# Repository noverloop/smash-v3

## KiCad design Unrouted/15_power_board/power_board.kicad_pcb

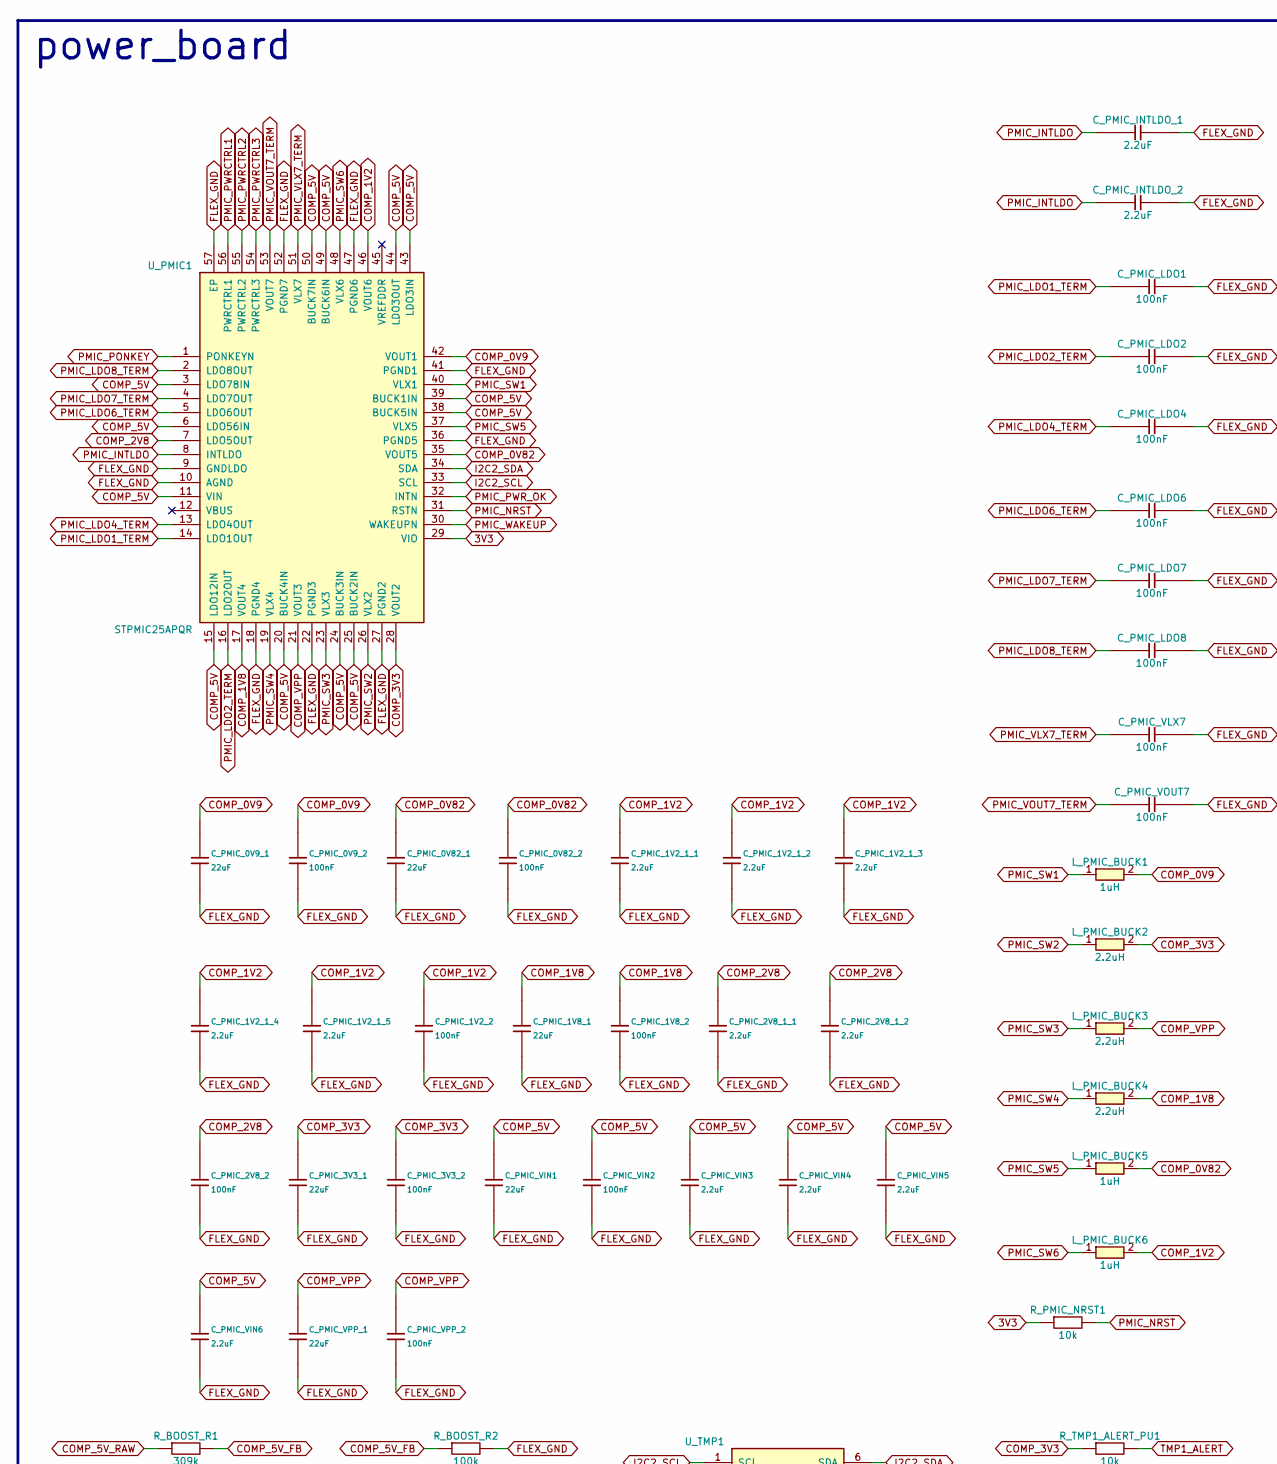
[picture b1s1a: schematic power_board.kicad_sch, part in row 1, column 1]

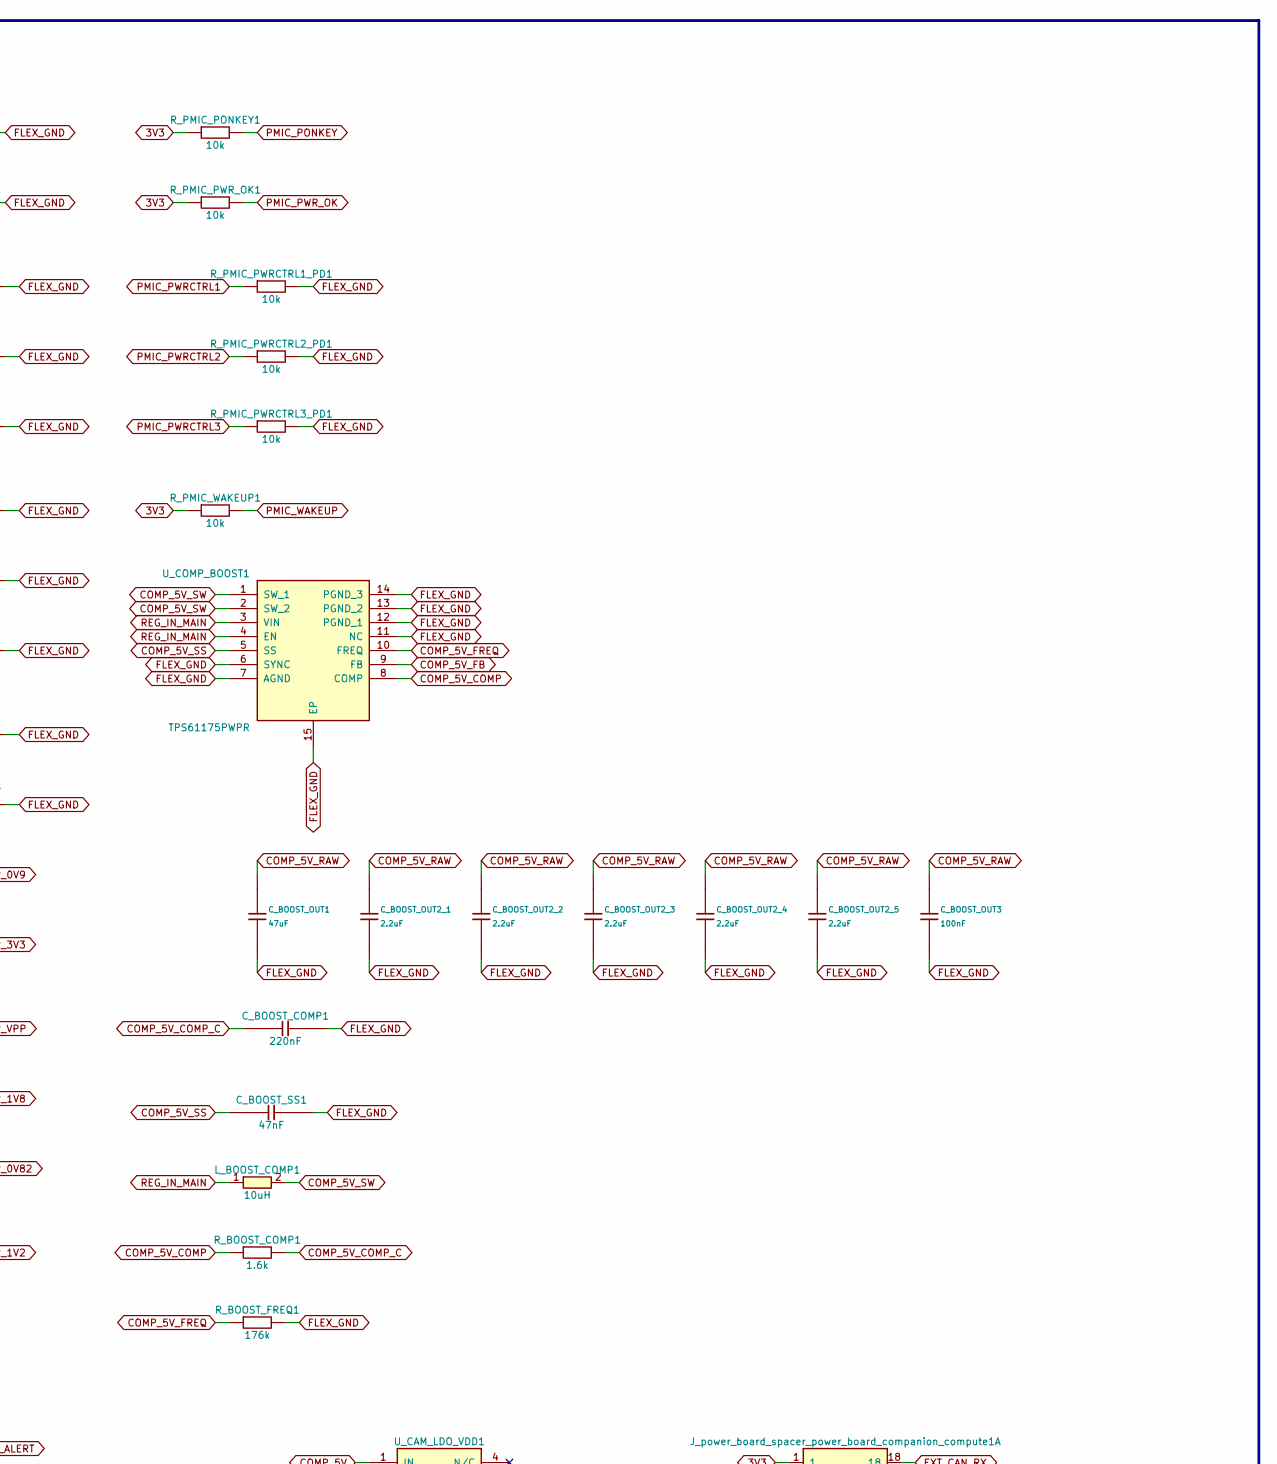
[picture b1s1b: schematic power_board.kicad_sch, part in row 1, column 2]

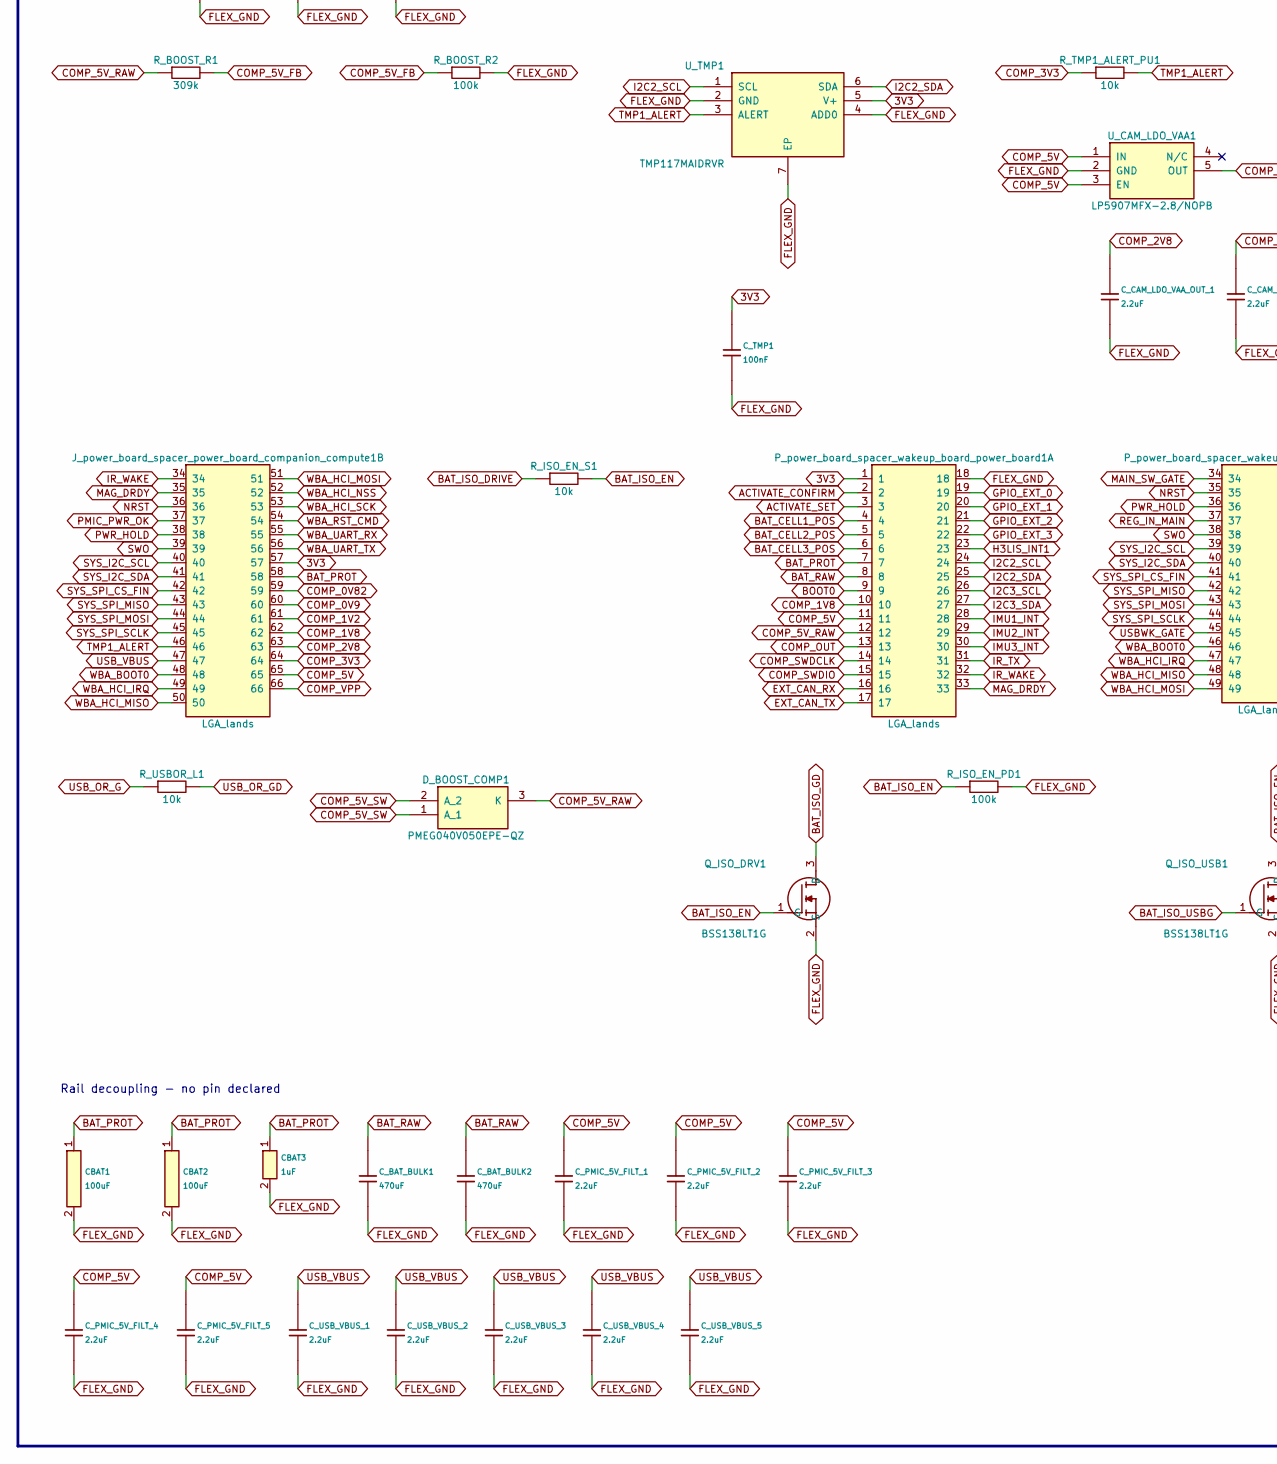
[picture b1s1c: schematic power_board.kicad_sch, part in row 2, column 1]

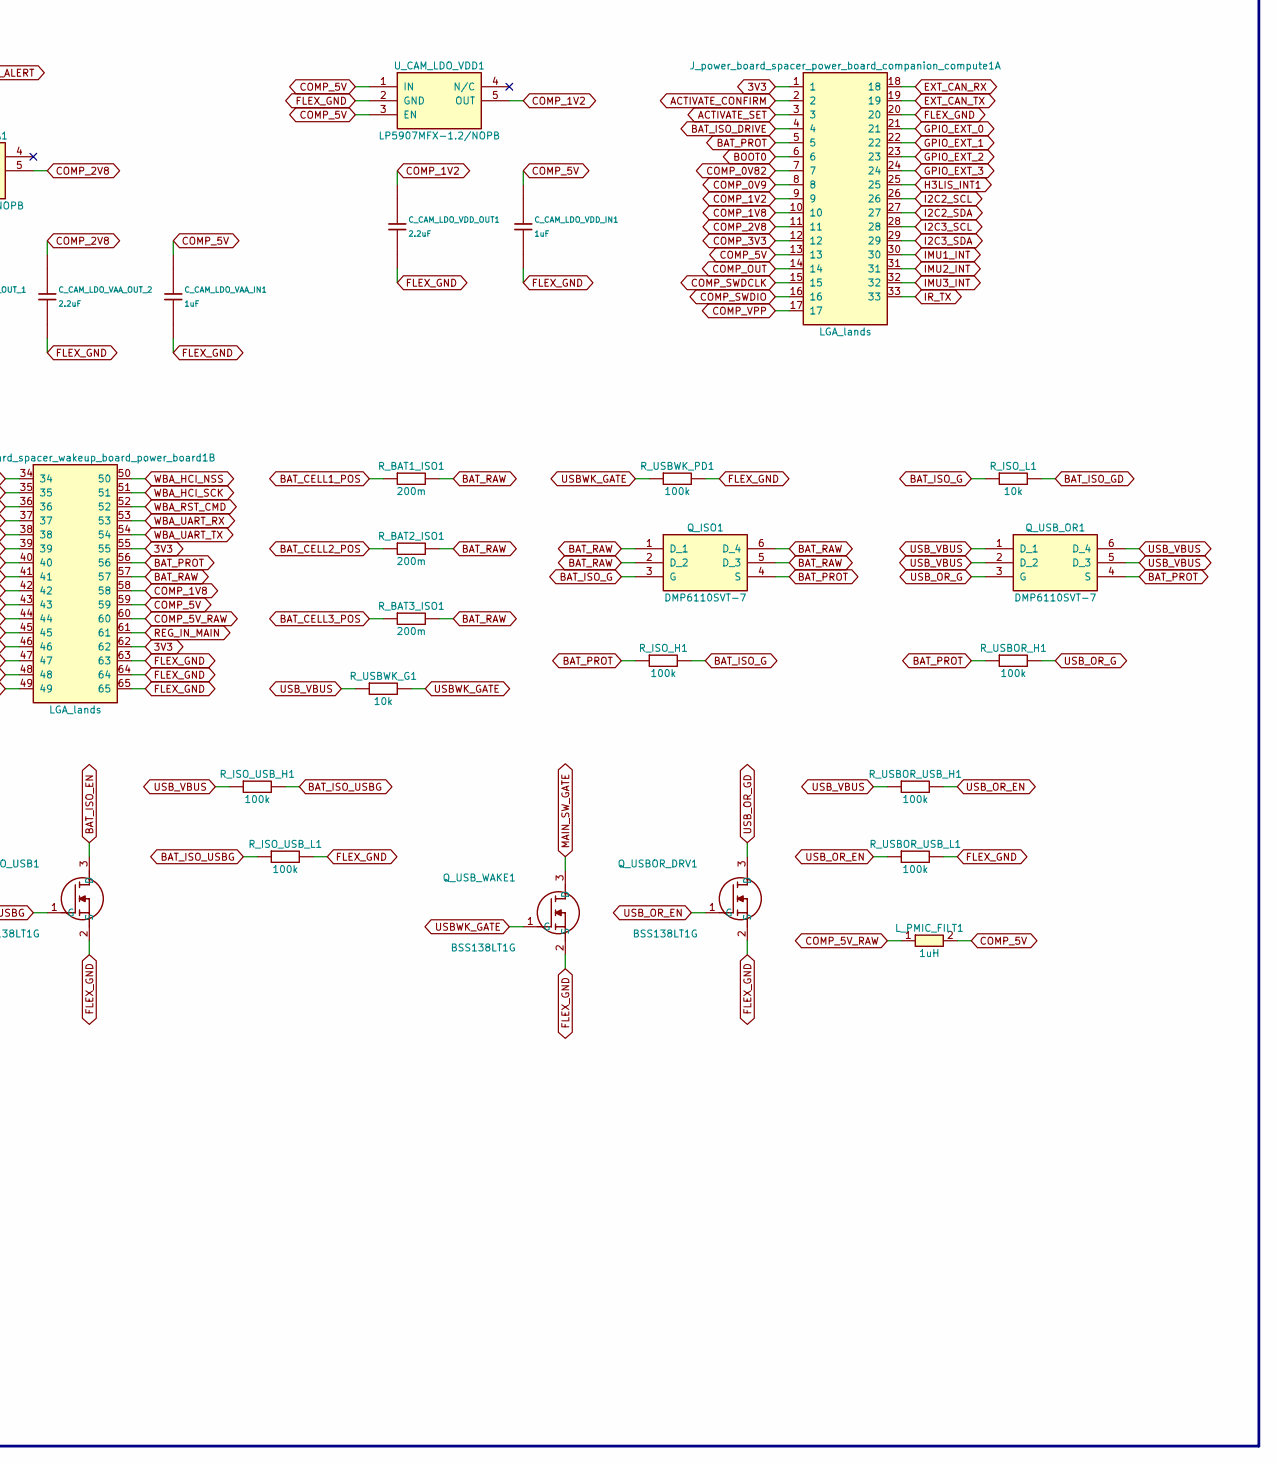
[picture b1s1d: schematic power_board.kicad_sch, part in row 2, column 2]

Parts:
CBAT1, CBAT2: 100uF; Capacitor_Tantalum_SMD_CP_EIA-7343-15_Kemet-W; MPN T528W 100uF (7343-15 thinnest variant)
CBAT3: 1uF; Capacitor_SMD_C_0805_2012Metric; MPN C-Series MIL-PRF-32535 X7R 0805 1uF
C_BAT_BULK1, C_BAT_BULK2: 470uF; Capacitor_Tantalum_SMD_CP_EIA-7343-15_Kemet-W; MPN T528W 470uF (7343-15 thinnest variant)
C_BOOST_COMP1: 220nF; Capacitor_SMD_C_0603_1608Metric; MPN C-Series MIL-PRF-32535 X7R 0603 220nF
C_BOOST_OUT1: 47uF; Capacitor_Tantalum_SMD_CP_EIA-7343-15_Kemet-W; MPN T528W 47uF (7343-15 thinnest variant)
C_BOOST_OUT2_1, C_BOOST_OUT2_2, C_BOOST_OUT2_3, C_BOOST_OUT2_4, C_BOOST_OUT2_5: 2.2uF; Capacitor_SMD_C_0603_1608Metric; MPN C-Series MIL-PRF-32535 X7R 0603 2.2uF
C_BOOST_OUT3: 100nF; Capacitor_SMD_C_0402_1005Metric; MPN C0402 X7R 100nF
C_BOOST_SS1: 47nF; Capacitor_SMD_C_0402_1005Metric; MPN C0402 X7R 47nF
C_CAM_LDO_VAA_IN1: 1uF; Capacitor_SMD_C_0805_2012Metric; MPN C-Series MIL-PRF-32535 X7R 0805 1uF
C_CAM_LDO_VAA_OUT_1, C_CAM_LDO_VAA_OUT_2: 2.2uF; Capacitor_SMD_C_0603_1608Metric; MPN C-Series MIL-PRF-32535 X7R 0603 2.2uF
C_CAM_LDO_VDD_IN1: 1uF; Capacitor_SMD_C_0805_2012Metric; MPN C-Series MIL-PRF-32535 X7R 0805 1uF
C_CAM_LDO_VDD_OUT1: 2.2uF; Capacitor_SMD_C_0603_1608Metric; MPN C-Series MIL-PRF-32535 X7R 0603 2.2uF
C_PMIC_0V9_1, C_PMIC_0V82_1, C_PMIC_1V8_1, C_PMIC_3V3_1: 22uF; Capacitor_Tantalum_SMD_CP_EIA-3528-12_Kemet-T; MPN T491T 22uF (3528-12 thinnest variant)
C_PMIC_0V9_2, C_PMIC_0V82_2, C_PMIC_1V2_2, C_PMIC_1V8_2, C_PMIC_2V8_2, C_PMIC_3V3_2: 100nF; Capacitor_SMD_C_0402_1005Metric; MPN C0402 X7R 100nF
C_PMIC_1V2_1_1, C_PMIC_1V2_1_2, C_PMIC_1V2_1_3, C_PMIC_1V2_1_4, C_PMIC_1V2_1_5, C_PMIC_2V8_1_1, C_PMIC_2V8_1_2, C_PMIC_5V_FILT_1, C_PMIC_5V_FILT_2, C_PMIC_5V_FILT_3, C_PMIC_5V_FILT_4, C_PMIC_5V_FILT_5: 2.2uF; Capacitor_SMD_C_0603_1608Metric; MPN C-Series MIL-PRF-32535 X7R 0603 2.2uF
C_PMIC_INTLDO_1, C_PMIC_INTLDO_2: 2.2uF; Capacitor_SMD_C_0603_1608Metric; MPN C-Series MIL-PRF-32535 X7R 0603 2.2uF
C_PMIC_LDO1, C_PMIC_LDO2, C_PMIC_LDO4, C_PMIC_LDO6, C_PMIC_LDO7, C_PMIC_LDO8: 100nF; Capacitor_SMD_C_0402_1005Metric; MPN C0402 X7R 100nF
C_PMIC_VIN1: 22uF; Capacitor_Tantalum_SMD_CP_EIA-3528-12_Kemet-T; MPN T491T 22uF (3528-12 thinnest variant)
C_PMIC_VIN2: 100nF; Capacitor_SMD_C_0402_1005Metric; MPN C0402 X7R 100nF
C_PMIC_VIN3, C_PMIC_VIN4, C_PMIC_VIN5, C_PMIC_VIN6: 2.2uF; Capacitor_SMD_C_0603_1608Metric; MPN C-Series MIL-PRF-32535 X7R 0603 2.2uF
C_PMIC_VLX7: 100nF; Capacitor_SMD_C_0402_1005Metric; MPN C0402 X7R 100nF
C_PMIC_VOUT7: 100nF; Capacitor_SMD_C_0402_1005Metric; MPN C0402 X7R 100nF
C_PMIC_VPP_1: 22uF; Capacitor_Tantalum_SMD_CP_EIA-3528-12_Kemet-T; MPN T491T 22uF (3528-12 thinnest variant)
C_PMIC_VPP_2: 100nF; Capacitor_SMD_C_0402_1005Metric; MPN C0402 X7R 100nF
C_TMP1: 100nF; Capacitor_SMD_C_0402_1005Metric; MPN C0402 X7R 100nF
C_USB_VBUS_1, C_USB_VBUS_2, C_USB_VBUS_3, C_USB_VBUS_4, C_USB_VBUS_5: 2.2uF; Capacitor_SMD_C_0603_1608Metric; MPN C-Series MIL-PRF-32535 X7R 0603 2.2uF
D_BOOST_COMP1: PMEG040V050EPE-QZ; PMEG040V050EPEQZ; MPN PMEG040V050EPE-QZ
J_power_board_spacer_power_board_companion_compute1: LGA_lands; J_power_board_spacer_power_board_companion_compute; MPN LGA_lands
L_BOOST_COMP1: 10uH; INDPM4848X280N; MPN 744043100
L_PMIC_BUCK1, L_PMIC_BUCK5, L_PMIC_BUCK6: 1uH; Inductor_SMD_L_2012_2.0x1.25mm; MPN TMS201210ALM-1R0MTAA
L_PMIC_BUCK2, L_PMIC_BUCK3, L_PMIC_BUCK4: 2.2uH; Inductor_SMD_L_2012_2.0x1.25mm; MPN TMS201210ALM-2R2MTAA
L_PMIC_FILT1: 1uH; Inductor_SMD_L_2012_2.0x1.25mm; MPN TMS201210ALM-1R0MTAA
P_power_board_spacer_wakeup_board_power_board1: LGA_lands; P_power_board_spacer_wakeup_board_power_board; MPN LGA_lands
Q_ISO1: DMP6110SVT-7; SOT95P280X100-6N; MPN DMP6110SVT-7
Q_ISO_DRV1: BSS138LT1G; SOT96P237X111-3N; MPN BSS138LT1G
Q_ISO_USB1: BSS138LT1G; SOT96P237X111-3N; MPN BSS138LT1G
Q_USBOR_DRV1: BSS138LT1G; SOT96P237X111-3N; MPN BSS138LT1G
Q_USB_OR1: DMP6110SVT-7; SOT95P280X100-6N; MPN DMP6110SVT-7
Q_USB_WAKE1: BSS138LT1G; SOT96P237X111-3N; MPN BSS138LT1G
R_BAT1_ISO1, R_BAT2_ISO1, R_BAT3_ISO1: 200m; Resistor_SMD_R_0402_1005Metric; MPN CRCW0402 200m 1% e3
R_BOOST_COMP1: 1.6k; Resistor_SMD_R_0402_1005Metric; MPN CRCW0402 1.6k 1% e3
R_BOOST_FREQ1: 176k; Resistor_SMD_R_0402_1005Metric; MPN CRCW0402 176k 1% e3
R_BOOST_R1: 309k; Resistor_SMD_R_0402_1005Metric; MPN CRCW0402 309k 1% e3
R_BOOST_R2: 100k; Resistor_SMD_R_0402_1005Metric; MPN CRCW0402 100k 1% e3
R_ISO_EN_PD1: 100k; Resistor_SMD_R_0402_1005Metric; MPN CRCW0402 100k 1% e3
R_ISO_EN_S1: 10k; Resistor_SMD_R_0402_1005Metric; MPN CRCW0402 10k 1% e3
R_ISO_H1: 100k; Resistor_SMD_R_0402_1005Metric; MPN CRCW0402 100k 1% e3
R_ISO_L1: 10k; Resistor_SMD_R_0402_1005Metric; MPN CRCW0402 10k 1% e3
R_ISO_USB_H1: 100k; Resistor_SMD_R_0402_1005Metric; MPN CRCW0402 100k 1% e3
R_ISO_USB_L1: 100k; Resistor_SMD_R_0402_1005Metric; MPN CRCW0402 100k 1% e3
R_PMIC_NRST1: 10k; Resistor_SMD_R_0402_1005Metric; MPN CRCW0402 10k 1% e3
R_PMIC_PONKEY1: 10k; Resistor_SMD_R_0402_1005Metric; MPN CRCW0402 10k 1% e3
R_PMIC_PWRCTRL1_PD1, R_PMIC_PWRCTRL2_PD1, R_PMIC_PWRCTRL3_PD1: 10k; Resistor_SMD_R_0402_1005Metric; MPN CRCW0402 10k 1% e3
R_PMIC_PWR_OK1: 10k; Resistor_SMD_R_0402_1005Metric; MPN CRCW0402 10k 1% e3
R_PMIC_WAKEUP1: 10k; Resistor_SMD_R_0402_1005Metric; MPN CRCW0402 10k 1% e3
R_TMP1_ALERT_PU1: 10k; Resistor_SMD_R_0402_1005Metric; MPN CRCW0402 10k 1% e3
R_USBOR_H1: 100k; Resistor_SMD_R_0402_1005Metric; MPN CRCW0402 100k 1% e3
R_USBOR_L1: 10k; Resistor_SMD_R_0402_1005Metric; MPN CRCW0402 10k 1% e3
R_USBOR_USB_H1: 100k; Resistor_SMD_R_0402_1005Metric; MPN CRCW0402 100k 1% e3
R_USBOR_USB_L1: 100k; Resistor_SMD_R_0402_1005Metric; MPN CRCW0402 100k 1% e3
R_USBWK_G1: 10k; Resistor_SMD_R_0402_1005Metric; MPN CRCW0402 10k 1% e3
R_USBWK_PD1: 100k; Resistor_SMD_R_0402_1005Metric; MPN CRCW0402 100k 1% e3
U_CAM_LDO_VAA1: LP5907MFX-2.8/NOPB; SOT95P280X145-5N; MPN LP5907MFX-2.8/NOPB
U_CAM_LDO_VDD1: LP5907MFX-1.2/NOPB; SOT95P280X145-5N; MPN LP5907MFX-1.2/NOPB
U_COMP_BOOST1: TPS61175PWPR; SOP65P640X120-15N; MPN TPS61175PWPR
U_PMIC1: STPMIC25APQR; QFN40P650X650X90-57N-D; MPN STPMIC25APQR
U_TMP1: TMP117MAIDRVR; SON65P200X200X80-7N; MPN TMP117MAIDRVR

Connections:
3V3: C_TMP1.1 (+), J_power_board_spacer_power_board_compan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.1, J_power_board_spacer_power_board_compan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.57, P_power_board_spacer_wakeup_board_power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.1, P_power_board_spacer_wakeup_board_power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.55, P_power_board_spacer_wakeup_board_power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.62, R_PMIC_NRST1.1, R_PMIC_PONKEY1.1, R_PMIC_PWR_OK1.1, R_PMIC_WAKEUP1.1, U_PMIC1.29 (VIO), U_TMP1.5 (V+)
ACTIVATE_CONFIRM: J_power_board_spacer_power_board_compan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.2, P_power_board_spacer_wakeup_board_power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.2
ACTIVATE_SET: J_power_board_spacer_power_board_compan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.3, P_power_board_spacer_wakeup_board_power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.3
BAT_CELL1_POS: P_power_board_spacer_wakeup_board_power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.4, R_BAT1_ISO1.1
BAT_CELL2_POS: P_power_board_spacer_wakeup_board_power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.5, R_BAT2_ISO1.1
BAT_CELL3_POS: P_power_board_spacer_wakeup_board_power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.6, R_BAT3_ISO1.1
BAT_ISO_DRIVE: J_power_board_spacer_power_board_compan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.4, R_ISO_EN_S1.1
BAT_ISO_EN: Q_ISO_DRV1.1 (G), Q_ISO_USB1.3 (D), R_ISO_EN_PD1.1, R_ISO_EN_S1.2
BAT_ISO_G: Q_ISO1.3 (G), R_ISO_H1.2, R_ISO_L1.1
BAT_ISO_GD: Q_ISO_DRV1.3 (D), R_ISO_L1.2
BAT_ISO_USBG: Q_ISO_USB1.1 (G), R_ISO_USB_H1.2, R_ISO_USB_L1.1
BAT_PROT: CBAT1.1 (+), CBAT2.1 (+), CBAT3.1, J_power_board_spacer_power_board_compan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.5, J_power_board_spacer_power_board_compan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.58, P_power_board_spacer_wakeup_board_power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.7, P_power_board_spacer_wakeup_board_power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.56, Q_ISO1.4 (S), Q_USB_OR1.4 (S), R_ISO_H1.1, R_USBOR_H1.1
BAT_RAW: C_BAT_BULK1.1 (+), C_BAT_BULK2.1 (+), P_power_board_spacer_wakeup_board_power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.8, P_power_board_spacer_wakeup_board_power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.57, Q_ISO1.1 (D_1), Q_ISO1.2 (D_2), Q_ISO1.5 (D_3), Q_ISO1.6 (D_4), R_BAT1_ISO1.2, R_BAT2_ISO1.2, R_BAT3_ISO1.2
BOOT0: J_power_board_spacer_power_board_compan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.6, P_power_board_spacer_wakeup_board_power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.9
COMP_0V9: C_PMIC_0V9_1.1 (+), C_PMIC_0V9_2.1 (+), J_power_board_spacer_power_board_compan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.8, J_power_board_spacer_power_board_compan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.60, L_PMIC_BUCK1.2, U_PMIC1.42 (VOUT1)
COMP_0V82: C_PMIC_0V82_1.1 (+), C_PMIC_0V82_2.1 (+), J_power_board_spacer_power_board_compan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.7, J_power_board_spacer_power_board_compan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.59, L_PMIC_BUCK5.2, U_PMIC1.35 (VOUT5)
COMP_1V2: C_CAM_LDO_VDD_OUT1.1 (+), C_PMIC_1V2_1_1.1 (+), C_PMIC_1V2_1_2.1 (+), C_PMIC_1V2_1_3.1 (+), C_PMIC_1V2_1_4.1 (+), C_PMIC_1V2_1_5.1 (+), C_PMIC_1V2_2.1 (+), J_power_board_spacer_power_board_compan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.9, J_power_board_spacer_power_board_compan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.61, L_PMIC_BUCK6.2, U_CAM_LDO_VDD1.5 (OUT), U_PMIC1.46 (VOUT6)
COMP_1V8: C_PMIC_1V8_1.1 (+), C_PMIC_1V8_2.1 (+), J_power_board_spacer_power_board_compan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.10, J_power_board_spacer_power_board_compan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.62, L_PMIC_BUCK4.2, P_power_board_spacer_wakeup_board_power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.10, P_power_board_spacer_wakeup_board_power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.58, U_PMIC1.17 (VOUT4)
COMP_2V8: C_CAM_LDO_VAA_OUT_1.1 (+), C_CAM_LDO_VAA_OUT_2.1 (+), C_PMIC_2V8_1_1.1 (+), C_PMIC_2V8_1_2.1 (+), C_PMIC_2V8_2.1 (+), J_power_board_spacer_power_board_compan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.11, J_power_board_spacer_power_board_compan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.63, U_CAM_LDO_VAA1.5 (OUT), U_PMIC1.7 (LDO5OUT)
COMP_3V3: C_PMIC_3V3_1.1 (+), C_PMIC_3V3_2.1 (+), J_power_board_spacer_power_board_compan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.12, J_power_board_spacer_power_board_compan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.64, L_PMIC_BUCK2.2, R_TMP1_ALERT_PU1.1, U_PMIC1.28 (VOUT2)
COMP_5V: C_CAM_LDO_VAA_IN1.1 (+), C_CAM_LDO_VDD_IN1.1 (+), C_PMIC_5V_FILT_1.1 (+), C_PMIC_5V_FILT_2.1 (+), C_PMIC_5V_FILT_3.1 (+), C_PMIC_5V_FILT_4.1 (+), C_PMIC_5V_FILT_5.1 (+), C_PMIC_VIN1.1 (+), C_PMIC_VIN2.1 (+), C_PMIC_VIN3.1 (+), C_PMIC_VIN4.1 (+), C_PMIC_VIN5.1 (+), C_PMIC_VIN6.1 (+), J_power_board_spacer_power_board_compan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.13, J_power_board_spacer_power_board_compan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.65, L_PMIC_FILT1.2, P_power_board_spacer_wakeup_board_power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.11, P_power_board_spacer_wakeup_board_power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.59, U_CAM_LDO_VAA1.1 (IN), U_CAM_LDO_VAA1.3 (EN), U_CAM_LDO_VDD1.1 (IN), U_CAM_LDO_VDD1.3 (EN), U_PMIC1.3 (LDO78IN), U_PMIC1.6 (LDO56IN), U_PMIC1.11 (VIN), U_PMIC1.15 (LDO12IN), U_PMIC1.20 (BUCK4IN), U_PMIC1.24 (BUCK3IN), U_PMIC1.25 (BUCK2IN), U_PMIC1.38 (BUCK5IN), U_PMIC1.39 (BUCK1IN), U_PMIC1.43 (LDO3IN), U_PMIC1.44 (LDO3OUT), U_PMIC1.49 (BUCK6IN), U_PMIC1.50 (BUCK7IN)
COMP_5V_COMP: R_BOOST_COMP1.1, U_COMP_BOOST1.8 (COMP)
COMP_5V_COMP_C: C_BOOST_COMP1.1 (+), R_BOOST_COMP1.2
COMP_5V_FB: R_BOOST_R1.2, R_BOOST_R2.1, U_COMP_BOOST1.9 (FB)
COMP_5V_FREQ: R_BOOST_FREQ1.1, U_COMP_BOOST1.10 (FREQ)
COMP_5V_RAW: C_BOOST_OUT1.1 (+), C_BOOST_OUT2_1.1 (+), C_BOOST_OUT2_2.1 (+), C_BOOST_OUT2_3.1 (+), C_BOOST_OUT2_4.1 (+), C_BOOST_OUT2_5.1 (+), C_BOOST_OUT3.1 (+), D_BOOST_COMP1.3 (K), L_PMIC_FILT1.1, P_power_board_spacer_wakeup_board_power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.12, P_power_board_spacer_wakeup_board_power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.60, R_BOOST_R1.1
COMP_5V_SS: C_BOOST_SS1.1 (+), U_COMP_BOOST1.5 (SS)
COMP_5V_SW: D_BOOST_COMP1.1 (A_1), D_BOOST_COMP1.2 (A_2), L_BOOST_COMP1.2, U_COMP_BOOST1.1 (SW_1), U_COMP_BOOST1.2 (SW_2)
COMP_OUT: J_power_board_spacer_power_board_compan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.14, P_power_board_spacer_wakeup_board_power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.13
COMP_SWDCLK: J_power_board_spacer_power_board_compan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.15, P_power_board_spacer_wakeup_board_power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.14
COMP_SWDIO: J_power_board_spacer_power_board_compan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.16, P_power_board_spacer_wakeup_board_power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.15
COMP_VPP: C_PMIC_VPP_1.1 (+), C_PMIC_VPP_2.1 (+), J_power_board_spacer_power_board_compan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.17, J_power_board_spacer_power_board_compan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.66, L_PMIC_BUCK3.2, U_PMIC1.21 (VOUT3)
EXT_CAN_RX: J_power_board_spacer_power_board_compan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.18, P_power_board_spacer_wakeup_board_power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.16
EXT_CAN_TX: J_power_board_spacer_power_board_compan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.19, P_power_board_spacer_wakeup_board_power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.17
FLEX_GND: CBAT1.2 (-), CBAT2.2 (-), CBAT3.2, C_BAT_BULK1.2 (-), C_BAT_BULK2.2 (-), C_BOOST_COMP1.2 (-), C_BOOST_OUT1.2 (-), C_BOOST_OUT2_1.2 (-), C_BOOST_OUT2_2.2 (-), C_BOOST_OUT2_3.2 (-), C_BOOST_OUT2_4.2 (-), C_BOOST_OUT2_5.2 (-), C_BOOST_OUT3.2 (-), C_BOOST_SS1.2 (-), C_CAM_LDO_VAA_IN1.2 (-), C_CAM_LDO_VAA_OUT_1.2 (-), C_CAM_LDO_VAA_OUT_2.2 (-), C_CAM_LDO_VDD_IN1.2 (-), C_CAM_LDO_VDD_OUT1.2 (-), C_PMIC_0V9_1.2 (-), C_PMIC_0V9_2.2 (-), C_PMIC_0V82_1.2 (-), C_PMIC_0V82_2.2 (-), C_PMIC_1V2_1_1.2 (-), C_PMIC_1V2_1_2.2 (-), C_PMIC_1V2_1_3.2 (-), C_PMIC_1V2_1_4.2 (-), C_PMIC_1V2_1_5.2 (-), C_PMIC_1V2_2.2 (-), C_PMIC_1V8_1.2 (-), C_PMIC_1V8_2.2 (-), C_PMIC_2V8_1_1.2 (-), C_PMIC_2V8_1_2.2 (-), C_PMIC_2V8_2.2 (-), C_PMIC_3V3_1.2 (-), C_PMIC_3V3_2.2 (-), C_PMIC_5V_FILT_1.2 (-), C_PMIC_5V_FILT_2.2 (-), C_PMIC_5V_FILT_3.2 (-), C_PMIC_5V_FILT_4.2 (-), C_PMIC_5V_FILT_5.2 (-), C_PMIC_INTLDO_1.2 (-), C_PMIC_INTLDO_2.2 (-), C_PMIC_LDO1.2 (-), C_PMIC_LDO2.2 (-), C_PMIC_LDO4.2 (-), C_PMIC_LDO6.2 (-), C_PMIC_LDO7.2 (-), C_PMIC_LDO8.2 (-), C_PMIC_VIN1.2 (-), C_PMIC_VIN2.2 (-), C_PMIC_VIN3.2 (-), C_PMIC_VIN4.2 (-), C_PMIC_VIN5.2 (-), C_PMIC_VIN6.2 (-), C_PMIC_VLX7.2 (-), C_PMIC_VOUT7.2 (-), C_PMIC_VPP_1.2 (-), C_PMIC_VPP_2.2 (-), C_TMP1.2 (-), C_USB_VBUS_1.2 (-), C_USB_VBUS_2.2 (-), C_USB_VBUS_3.2 (-), C_USB_VBUS_4.2 (-), C_USB_VBUS_5.2 (-), J_power_board_spacer_power_board_compan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.20, P_power_board_spacer_wakeup_board_power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.18, P_power_board_spacer_wakeup_board_power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.63, P_power_board_spacer_wakeup_board_power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.64, P_power_board_spacer_wakeup_board_power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.65, Q_ISO_DRV1.2 (S), Q_ISO_USB1.2 (S), Q_USBOR_DRV1.2 (S), Q_USB_WAKE1.2 (S), R_BOOST_FREQ1.2, R_BOOST_R2.2, R_ISO_EN_PD1.2, R_ISO_USB_L1.2, R_PMIC_PWRCTRL1_PD1.2, R_PMIC_PWRCTRL2_PD1.2, R_PMIC_PWRCTRL3_PD1.2, R_USBOR_USB_L1.2, R_USBWK_PD1.2, U_CAM_LDO_VAA1.2 (GND), U_CAM_LDO_VDD1.2 (GND), U_COMP_BOOST1.6 (SYNC), U_COMP_BOOST1.7 (AGND), U_COMP_BOOST1.11 (NC), U_COMP_BOOST1.12 (PGND_1), U_COMP_BOOST1.13 (PGND_2), U_COMP_BOOST1.14 (PGND_3), U_COMP_BOOST1.15 (EP), U_PMIC1.9 (GNDLDO), U_PMIC1.10 (AGND), U_PMIC1.18 (PGND4), U_PMIC1.22 (PGND3), U_PMIC1.27 (PGND2), U_PMIC1.36 (PGND5), U_PMIC1.41 (PGND1), U_PMIC1.47 (PGND6), U_PMIC1.52 (PGND7), U_PMIC1.57 (EP), U_TMP1.2 (GND), U_TMP1.4 (ADD0), U_TMP1.7 (EP)
GPIO_EXT_0: J_power_board_spacer_power_board_compan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.21, P_power_board_spacer_wakeup_board_power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.19
GPIO_EXT_1: J_power_board_spacer_power_board_compan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.22, P_power_board_spacer_wakeup_board_power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.20
GPIO_EXT_2: J_power_board_spacer_power_board_compan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.23, P_power_board_spacer_wakeup_board_power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.21
GPIO_EXT_3: J_power_board_spacer_power_board_compan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.24, P_power_board_spacer_wakeup_board_power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.22
H3LIS_INT1: J_power_board_spacer_power_board_compan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.25, P_power_board_spacer_wakeup_board_power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.23
I2C2_SCL: J_power_board_spacer_power_board_compan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.26, P_power_board_spacer_wakeup_board_power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.24, U_PMIC1.33 (SCL), U_TMP1.1 (SCL)
I2C2_SDA: J_power_board_spacer_power_board_compan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.27, P_power_board_spacer_wakeup_board_power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.25, U_PMIC1.34 (SDA), U_TMP1.6 (SDA)
I2C3_SCL: J_power_board_spacer_power_board_compan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.28, P_power_board_spacer_wakeup_board_power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.26
I2C3_SDA: J_power_board_spacer_power_board_compan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.29, P_power_board_spacer_wakeup_board_power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.27
IMU1_INT: J_power_board_spacer_power_board_compan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.30, P_power_board_spacer_wakeup_board_power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.28
IMU2_INT: J_power_board_spacer_power_board_compan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.31, P_power_board_spacer_wakeup_board_power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.29
IMU3_INT: J_power_board_spacer_power_board_compan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.32, P_power_board_spacer_wakeup_board_power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.30
IR_TX: J_power_board_spacer_power_board_compan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.33, P_power_board_spacer_wakeup_board_power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.31
IR_WAKE: J_power_board_spacer_power_board_compan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.34, P_power_board_spacer_wakeup_board_power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.32
MAG_DRDY: J_power_board_spacer_power_board_compan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.35, P_power_board_spacer_wakeup_board_power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.33
MAIN_SW_GATE: P_power_board_spacer_wakeup_board_power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.34, Q_USB_WAKE1.3 (D)
NRST: J_power_board_spacer_power_board_compan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.36, P_power_board_spacer_wakeup_board_power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.35
PMIC_INTLDO: C_PMIC_INTLDO_1.1 (+), C_PMIC_INTLDO_2.1 (+), U_PMIC1.8 (INTLDO)
PMIC_LDO1_TERM: C_PMIC_LDO1.1 (+), U_PMIC1.14 (LDO1OUT)
PMIC_LDO2_TERM: C_PMIC_LDO2.1 (+), U_PMIC1.16 (LDO2OUT)
PMIC_LDO4_TERM: C_PMIC_LDO4.1 (+), U_PMIC1.13 (LDO4OUT)
PMIC_LDO6_TERM: C_PMIC_LDO6.1 (+), U_PMIC1.5 (LDO6OUT)
PMIC_LDO7_TERM: C_PMIC_LDO7.1 (+), U_PMIC1.4 (LDO7OUT)
PMIC_LDO8_TERM: C_PMIC_LDO8.1 (+), U_PMIC1.2 (LDO8OUT)
PMIC_NRST: R_PMIC_NRST1.2, U_PMIC1.31 (RSTN)
PMIC_PONKEY: R_PMIC_PONKEY1.2, U_PMIC1.1 (PONKEYN)
PMIC_PWRCTRL1: R_PMIC_PWRCTRL1_PD1.1, U_PMIC1.56 (PWRCTRL1)
PMIC_PWRCTRL2: R_PMIC_PWRCTRL2_PD1.1, U_PMIC1.55 (PWRCTRL2)
PMIC_PWRCTRL3: R_PMIC_PWRCTRL3_PD1.1, U_PMIC1.54 (PWRCTRL3)
PMIC_PWR_OK: J_power_board_spacer_power_board_compan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.37, R_PMIC_PWR_OK1.2, U_PMIC1.32 (INTN)
PMIC_SW1: L_PMIC_BUCK1.1, U_PMIC1.40 (VLX1)
PMIC_SW2: L_PMIC_BUCK2.1, U_PMIC1.26 (VLX2)
PMIC_SW3: L_PMIC_BUCK3.1, U_PMIC1.23 (VLX3)
PMIC_SW4: L_PMIC_BUCK4.1, U_PMIC1.19 (VLX4)
PMIC_SW5: L_PMIC_BUCK5.1, U_PMIC1.37 (VLX5)
PMIC_SW6: L_PMIC_BUCK6.1, U_PMIC1.48 (VLX6)
PMIC_VLX7_TERM: C_PMIC_VLX7.1 (+), U_PMIC1.51 (VLX7)
PMIC_VOUT7_TERM: C_PMIC_VOUT7.1 (+), U_PMIC1.53 (VOUT7)
PMIC_WAKEUP: R_PMIC_WAKEUP1.2, U_PMIC1.30 (WAKEUPN)
PWR_HOLD: J_power_board_spacer_power_board_compan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.38, P_power_board_spacer_wakeup_board_power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.36
REG_IN_MAIN: L_BOOST_COMP1.1, P_power_board_spacer_wakeup_board_power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.37, P_power_board_spacer_wakeup_board_power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.61, U_COMP_BOOST1.3 (VIN), U_COMP_BOOST1.4 (EN)
SWO: J_power_board_spacer_power_board_compan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.39, P_power_board_spacer_wakeup_board_power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.38
SYS_I2C_SCL: J_power_board_spacer_power_board_compan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.40, P_power_board_spacer_wakeup_board_power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.39
SYS_I2C_SDA: J_power_board_spacer_power_board_compan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.41, P_power_board_spacer_wakeup_board_power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.40
SYS_SPI_CS_FIN: J_power_board_spacer_power_board_compan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.42, P_power_board_spacer_wakeup_board_power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.41
SYS_SPI_MISO: J_power_board_spacer_power_board_compan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.43, P_power_board_spacer_wakeup_board_power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.42
SYS_SPI_MOSI: J_power_board_spacer_power_board_compan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.44, P_power_board_spacer_wakeup_board_power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.43
SYS_SPI_SCLK: J_power_board_spacer_power_board_compan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.45, P_power_board_spacer_wakeup_board_power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.44
TMP1_ALERT: J_power_board_spacer_power_board_compan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.46, R_TMP1_ALERT_PU1.2, U_TMP1.3 (ALERT)
USBWK_GATE: P_power_board_spacer_wakeup_board_power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.45, Q_USB_WAKE1.1 (G), R_USBWK_G1.2, R_USBWK_PD1.1
USB_OR_EN: Q_USBOR_DRV1.1 (G), R_USBOR_USB_H1.2, R_USBOR_USB_L1.1
USB_OR_G: Q_USB_OR1.3 (G), R_USBOR_H1.2, R_USBOR_L1.1
USB_OR_GD: Q_USBOR_DRV1.3 (D), R_USBOR_L1.2
USB_VBUS: C_USB_VBUS_1.1 (+), C_USB_VBUS_2.1 (+), C_USB_VBUS_3.1 (+), C_USB_VBUS_4.1 (+), C_USB_VBUS_5.1 (+), J_power_board_spacer_power_board_compan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.47, Q_USB_OR1.1 (D_1), Q_USB_OR1.2 (D_2), Q_USB_OR1.5 (D_3), Q_USB_OR1.6 (D_4), R_ISO_USB_H1.1, R_USBOR_USB_H1.1, R_USBWK_G1.1
WBA_BOOT0: J_power_board_spacer_power_board_compan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.48, P_power_board_spacer_wakeup_board_power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.46
WBA_HCI_IRQ: J_power_board_spacer_power_board_compan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.49, P_power_board_spacer_wakeup_board_power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.47
WBA_HCI_MISO: J_power_board_spacer_power_board_compan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.50, P_power_board_spacer_wakeup_board_power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.48
WBA_HCI_MOSI: J_power_board_spacer_power_board_compan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.51, P_power_board_spacer_wakeup_board_power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.49
WBA_HCI_NSS: J_power_board_spacer_power_board_compan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.52, P_power_board_spacer_wakeup_board_power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.50
WBA_HCI_SCK: J_power_board_spacer_power_board_compan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.53, P_power_board_spacer_wakeup_board_power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.51
WBA_RST_CMD: J_power_board_spacer_power_board_compan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.54, P_power_board_spacer_wakeup_board_power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.52
WBA_UART_RX: J_power_board_spacer_power_board_compan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.55, P_power_board_spacer_wakeup_board_power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.53
WBA_UART_TX: J_power_board_spacer_power_board_compan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.56, P_power_board_spacer_wakeup_board_power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.54

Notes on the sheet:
power_board
Rail decoupling - no pin declared

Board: 14 copper layers, 116 parts (45 on the bottom side), 98 nets, no tracks yet.

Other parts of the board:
MH1, MH2: smash_mech_potting

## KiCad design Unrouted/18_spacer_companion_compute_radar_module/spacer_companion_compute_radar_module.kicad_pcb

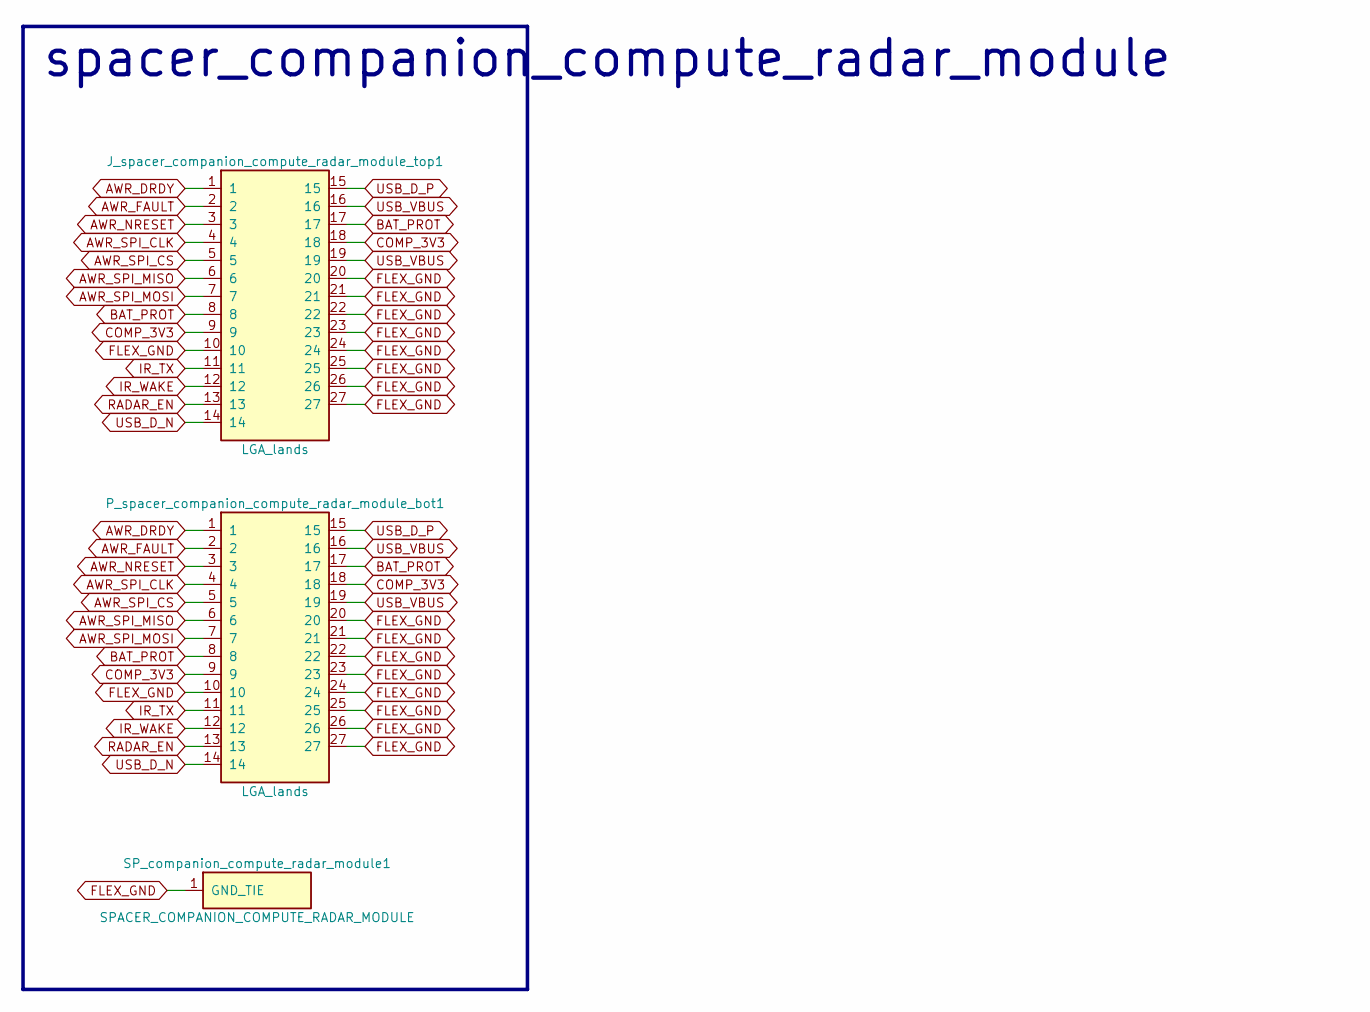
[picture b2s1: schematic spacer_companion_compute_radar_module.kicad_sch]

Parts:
J_spacer_companion_compute_radar_module_top1: LGA_lands; J_spacer_companion_compute_radar_module_top; MPN LGA_lands
P_spacer_companion_compute_radar_module_bot1: LGA_lands; P_spacer_companion_compute_radar_module_bot; MPN LGA_lands
SP_companion_compute_radar_module1: SPACER_COMPANION_COMPUTE_RADAR_MODULE; Spacer_Mechanical_34mm

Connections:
AWR_DRDY: J_spacer_companion_compute_radar_module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.1, P_spacer_companion_compute_radar_module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.1
AWR_FAULT: J_spacer_companion_compute_radar_module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.2, P_spacer_companion_compute_radar_module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.2
AWR_NRESET: J_spacer_companion_compute_radar_module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.3, P_spacer_companion_compute_radar_module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.3
AWR_SPI_CLK: J_spacer_companion_compute_radar_module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.4, P_spacer_companion_compute_radar_module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.4
AWR_SPI_CS: J_spacer_companion_compute_radar_module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.5, P_spacer_companion_compute_radar_module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.5
AWR_SPI_MISO: J_spacer_companion_compute_radar_module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.6, P_spacer_companion_compute_radar_module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.6
AWR_SPI_MOSI: J_spacer_companion_compute_radar_module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.7, P_spacer_companion_compute_radar_module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.7
BAT_PROT: J_spacer_companion_compute_radar_module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.8, J_spacer_companion_compute_radar_module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.17, P_spacer_companion_compute_radar_module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.8, P_spacer_companion_compute_radar_module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.17
COMP_3V3: J_spacer_companion_compute_radar_module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.9, J_spacer_companion_compute_radar_module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.18, P_spacer_companion_compute_radar_module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.9, P_spacer_companion_compute_radar_module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.18
FLEX_GND: J_spacer_companion_compute_radar_module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.10, J_spacer_companion_compute_radar_module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.20, J_spacer_companion_compute_radar_module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.21, J_spacer_companion_compute_radar_module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.22, J_spacer_companion_compute_radar_module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.23, J_spacer_companion_compute_radar_module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.24, J_spacer_companion_compute_radar_module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.25, J_spacer_companion_compute_radar_module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.26, J_spacer_companion_compute_radar_module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.27, P_spacer_companion_compute_radar_module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.10, P_spacer_companion_compute_radar_module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.20, P_spacer_companion_compute_radar_module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.21, P_spacer_companion_compute_radar_module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.22, P_spacer_companion_compute_radar_module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.23, P_spacer_companion_compute_radar_module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.24, P_spacer_companion_compute_radar_module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.25, P_spacer_companion_compute_radar_module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.26, P_spacer_companion_compute_radar_module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.27, SP_companion_compute_radar_module1.1
IR_TX: J_spacer_companion_compute_radar_module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.11, P_spacer_companion_compute_radar_module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.11
IR_WAKE: J_spacer_companion_compute_radar_module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.12, P_spacer_companion_compute_radar_module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.12
RADAR_EN: J_spacer_companion_compute_radar_module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.13, P_spacer_companion_compute_radar_module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.13
USB_D_N: J_spacer_companion_compute_radar_module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.14, P_spacer_companion_compute_radar_module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.14
USB_D_P: J_spacer_companion_compute_radar_module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.15, P_spacer_companion_compute_radar_module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.15
USB_VBUS: J_spacer_companion_compute_radar_module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.16, J_spacer_companion_compute_radar_module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.19, P_spacer_companion_compute_radar_module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.16, P_spacer_companion_compute_radar_module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.19

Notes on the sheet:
spacer_companion_compute_radar_module

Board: 2 copper layers, 5 parts (1 on the bottom side), 16 nets, no tracks yet.

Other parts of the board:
MH1, MH2: smash_mech_potting
